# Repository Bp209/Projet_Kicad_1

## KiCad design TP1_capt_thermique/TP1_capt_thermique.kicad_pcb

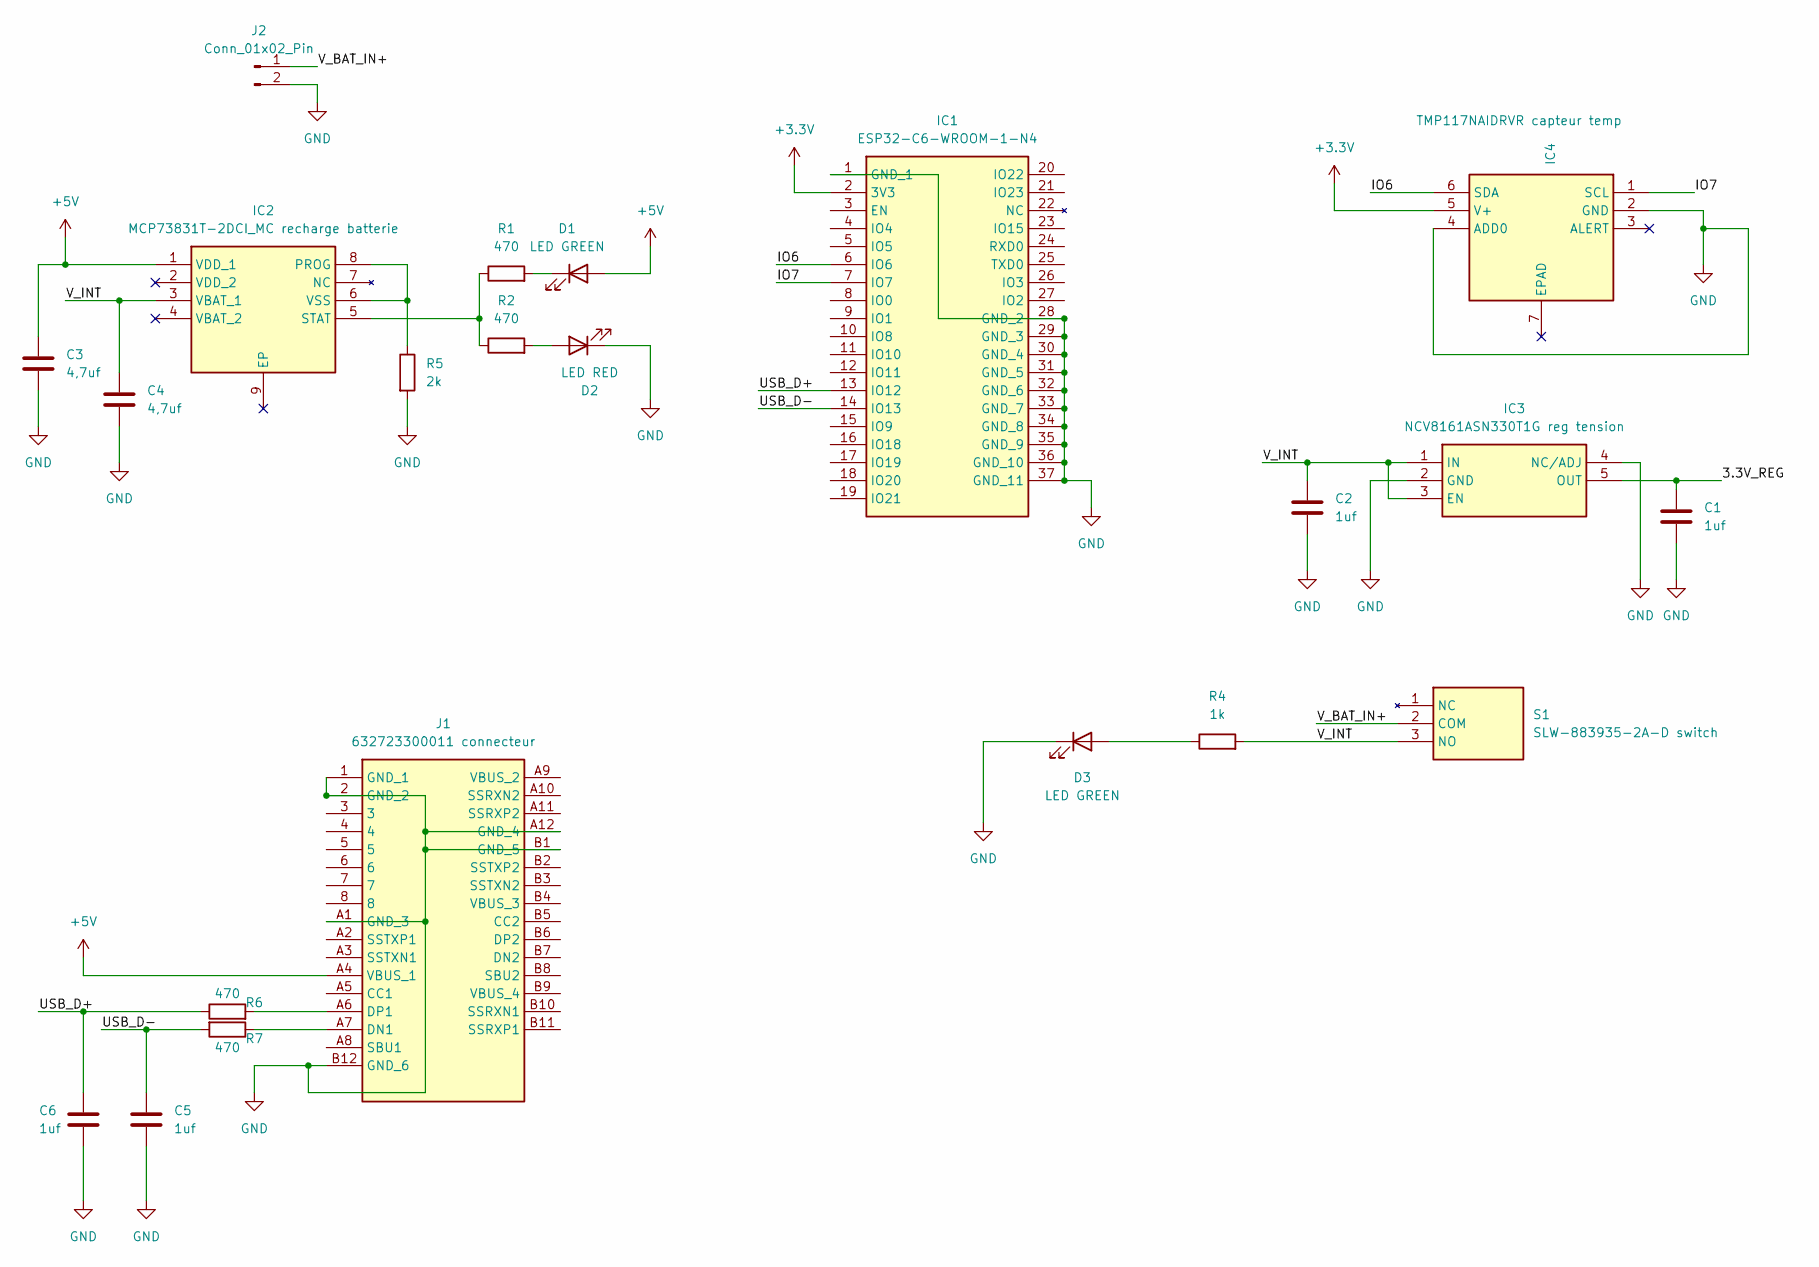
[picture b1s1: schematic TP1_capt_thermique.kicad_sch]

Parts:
C1, C2, C5, C6: 1uf; C_0402_1005Metric
C3, C4: 4,7uf; C_0402_1005Metric
D1, D3: LED GREEN; LED_0201_0603Metric
D2: LED RED; LED_0201_0603Metric
IC1: ESP32-C6-WROOM-1-N4; ESP32C6WROOM1N4; Mouser Part Number 356-ESP32C6WROOM1N4
IC2: MCP73831T-2DCI_MC recharge batterie; SON50P300X200X100-9N-D; Mouser Part Number 579-MCP73831T-2DCIMC
IC3: NCV8161ASN330T1G reg tension; SOT95P275X110-5N; Mouser Part Number 863-NCV8161ASN330T1G
IC4: TMP117NAIDRVR capteur temp; SON65P200X200X80-7N; Mouser Part Number 595-TMP117NAIDRVR
J1: 632723300011 connecteur; 632723300011; Mouser Part Number 710-632723300011
J2: Conn_01x02_Pin; JWT_A3963_1x02_P3.96mm_Vertical
R1, R2, R6, R7: 470; R_0402_1005Metric
R4: 1k; R_0402_1005Metric
R5: 2k; R_0402_1005Metric
S1: SLW-883935-2A-D switch; SLW8839352AD; Mouser Part Number 179-SLW-883935-2A-D

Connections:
+3.3V: IC1.2 (3V3), IC4.5 (V+)
+5V: C3.1, D1.2 (A), IC2.1 (VDD_1), J1.A4 (VBUS_1)
/3.3V_REG: C1.1, IC3.5 (OUT)
/IO6: IC1.6 (IO6), IC4.6 (SDA)
/IO7: IC1.7 (IO7), IC4.1 (SCL)
/USB_D+: C6.1, IC1.13 (IO12), R6.1
/USB_D-: C5.1, IC1.14 (IO13), R7.2
/V_BAT_IN+: J2.1, S1.2 (COM)
/V_INT: C2.1, C4.1, IC2.3 (VBAT_1), IC3.1 (IN), IC3.3 (EN), R4.2, S1.3 (NO)
GND: C1.2, C2.2, C3.2, C4.2, C5.2, C6.2, D2.1 (K), D3.1 (K), IC1.1 (GND_1), IC1.28 (GND_2), IC1.29 (GND_3), IC1.30 (GND_4), IC1.31 (GND_5), IC1.32 (GND_6), IC1.33 (GND_7), IC1.34 (GND_8), IC1.35 (GND_9), IC1.36 (GND_10), IC1.37 (GND_11), IC3.2 (GND), IC3.4 (NC/ADJ), IC4.2 (GND), IC4.4 (ADD0), J1.1 (GND_1), J1.2 (GND_2), J1.A1 (GND_3), J1.A12 (GND_4), J1.B1 (GND_5), J1.B12 (GND_6), J2.2, R5.2
unnamed: D1.1 (K), R1.2
unnamed: D2.2 (A), R2.2
unnamed: D3.2 (A), R4.1
unnamed: IC2.6 (VSS), IC2.8 (PROG), R5.1
unnamed: IC2.5 (STAT), R1.1, R2.1
unnamed: J1.A7 (DN1), R7.1
unnamed: J1.A6 (DP1), R6.2

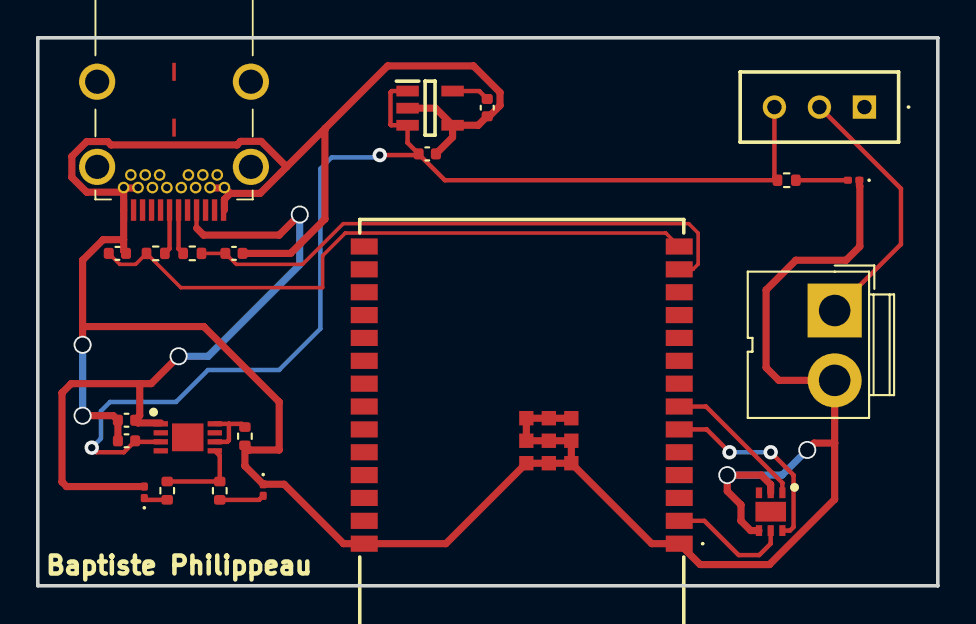
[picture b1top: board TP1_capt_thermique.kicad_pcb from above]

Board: 2 copper layers, 50.0 x 30.4 mm, 22 parts (0 on the bottom side), 17 nets.

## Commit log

2023-10-25 projet IOT 1 par Baptiste Philippeau
    Kicad + rapport word du premier projet
